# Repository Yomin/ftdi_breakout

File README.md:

# FTDI Breakout Board

Makes all pins of FT232RL available. Also has LED at CBUS2 for simple use of eg RxTx activity.

## License

MIT

## Parts

qty|name
---|---
1|FT232RL
1|USB B jack
1|4.7uF elko
2|100nF
2|8pin header
2|3mm led
2|resistor for led

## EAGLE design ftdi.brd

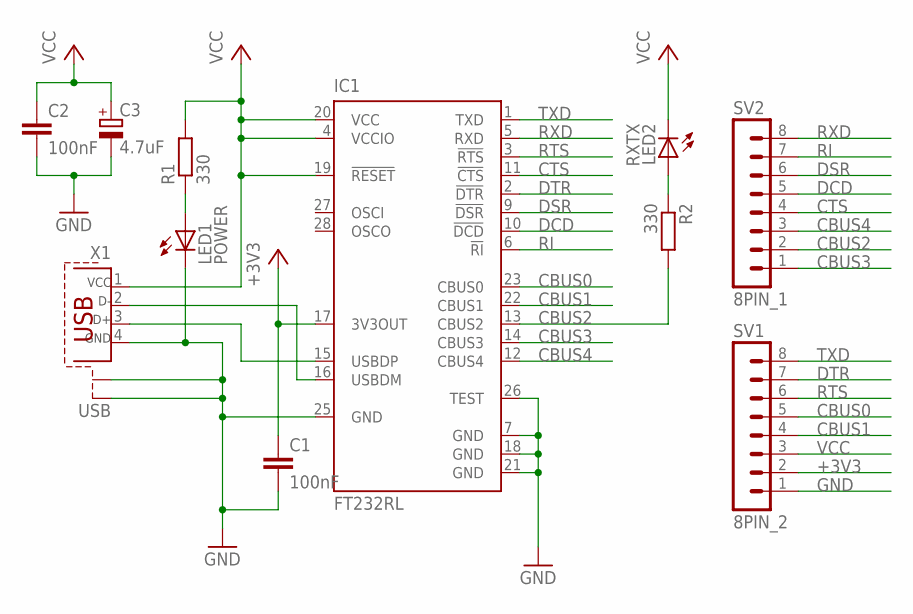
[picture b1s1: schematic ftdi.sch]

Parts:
C1, C2: 100nF; C050-024X044
C3: 4.7uF; E5-4
IC1: FT232RL; SSOP28
LED1: POWER; LED3MM
LED2: RXTX; LED3MM
R1, R2: 330; 0204/7
SV1: 8PIN_2; MA08-1
SV2: 8PIN_1; MA08-1
X1: USB; PN61729-S

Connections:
+3V3: C1.1, IC1.17 (3V3OUT), SV1.2
CBUS0: IC1.23 (CBUS0), SV1.5
CBUS1: IC1.22 (CBUS1), SV1.4
CBUS2: IC1.13 (CBUS2), R2.2, SV2.2
CBUS3: IC1.14 (CBUS3), SV2.1
CBUS4: IC1.12 (CBUS4), SV2.3
CTS: IC1.11 (!CTS), SV2.4
DCD: IC1.10 (!DCD), SV2.5
DSR: IC1.9 (!DSR), SV2.6
DTR: IC1.2 (!DTR), SV1.7
GND: C1.2, C2.2, C3.-, IC1.7 (GND), IC1.18 (GND), IC1.21 (GND), IC1.25 (GND), IC1.26 (TEST), LED1.K (C), SV1.1, X1.4, X1.S1, X1.S2
unnamed: LED1.A, R1.1
unnamed: IC1.16 (USBDM), X1.2
unnamed: IC1.15 (USBDP), X1.3
unnamed: LED2.A, R2.1
RI: IC1.6 (!RI), SV2.7
RTS: IC1.3 (!RTS), SV1.6
RXD: IC1.5 (RXD), SV2.8
TXD: IC1.1 (TXD), SV1.8
VCC: C2.1, C3.+, IC1.4 (VCCIO), IC1.19 (!RESET), IC1.20 (VCC), LED2.K (C), R1.2, SV1.3, X1.1

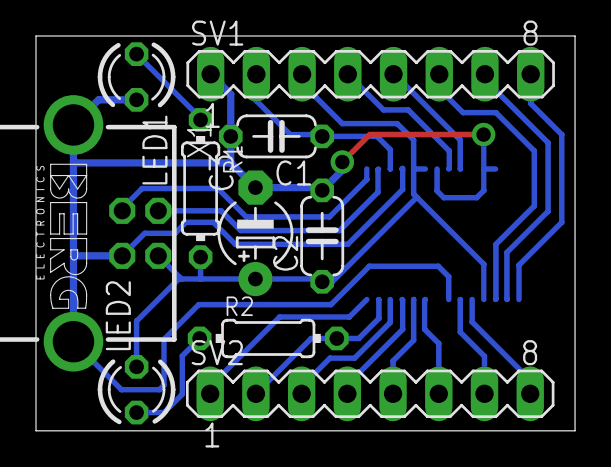
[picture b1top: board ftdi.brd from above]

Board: 2 copper layers, 29.9 x 21.9 mm, 11 parts (1 on the bottom side), 20 nets.

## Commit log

2013-03-22 init
